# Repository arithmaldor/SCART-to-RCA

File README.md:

# Copyright and Disclaimer
Copyright: Jacob Proctor 2018

This documentation describes Open Hardware and is licensed under the
CERN OHL v. 1.2.

You may redistribute and modify this documentation under the terms of the
CERN OHL v.1.2. (http://ohwr.org/cernohl). This documentation is distributed
WITHOUT ANY EXPRESS OR IMPLIED WARRANTY, INCLUDING OF
MERCHANTABILITY, SATISFACTORY QUALITY AND FITNESS FOR A
PARTICULAR PURPOSE. Please see the CERN OHL v.1.2 for applicable
conditions

# SCART to RCA Board

The goal of this project was to make an affordable open-source way to connect SCART cables to PVMs' or Crosspoint Switches. This is designed so
that the cables will be in line, and you can mount multiple of these boards in a row for crosspoint switches. Use with either RCA cables and RCA
female to male BNC adapters or RCA male to BNC female adapters and BNC cables. Use high quality adapters and cables for best results.

# Parts

SCART Connector: K-SCARTX-024, available on Mouser

RCA Connector: PJRAS3X2S01 is available on Mouser and Digikey, but the colors are wrong. Here are the ones I used, a bit cheaper per part:

https://www.ebay.com/itm/QTY-10-6-WAY-PCB-FEMALE-RCA-JACKS-GREEN-YELLOW-BLUE-WHITE-RED-RED-RCA-268N1-14/112220720415?var=null

Mounting hole size is M3, can be used with motherboard standoffs for mounting on MDF or acrylic or something else.

# Price Breakdown
$7.45 per board from OSHPark

$1.00 per RCA connector

$2.50 per SCART connector

Total per board: ~$11

# Version 0.1
This board is untested, I will probably be ordering a few soon after which I will update the version number to 1.0 if everything works out.

# OSHPark
https://oshpark.com/shared_projects/7CGRR3nm

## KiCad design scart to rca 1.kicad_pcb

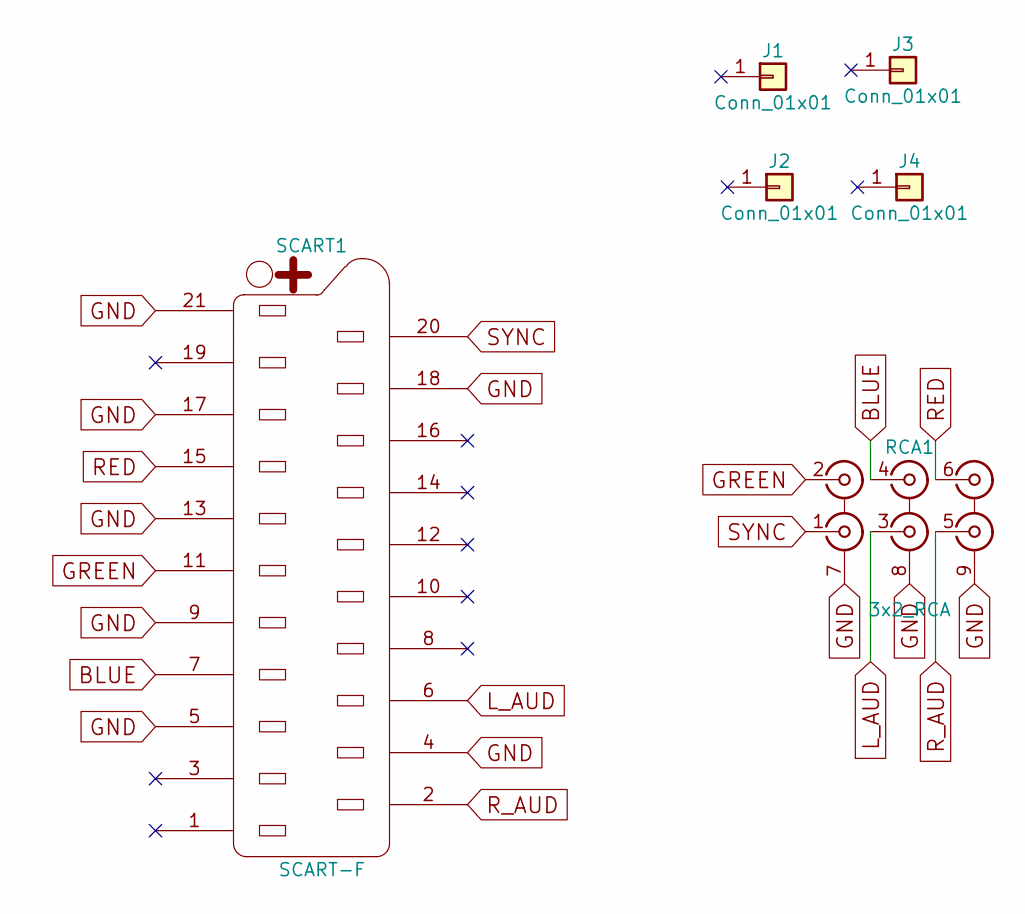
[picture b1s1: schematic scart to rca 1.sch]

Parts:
J1, J2, J3, J4: Conn_01x01; MountingHole_3.2mm_M3
RCA1: 3x2_RCA
SCART1: SCART-F; SCART_F

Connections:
BLUE: RCA1.4 (INGRN), SCART1.7
GND: RCA1.7 (GND), RCA1.8 (GND), RCA1.9 (GND), SCART1.4, SCART1.5, SCART1.9, SCART1.13, SCART1.17, SCART1.18, SCART1.21
GREEN: RCA1.2 (INRED), SCART1.11
L_AUD: RCA1.3 (INLAU), SCART1.6
RED: RCA1.6 (INBLU), SCART1.15
R_AUD: RCA1.5 (INRAU), SCART1.2
SYNC: RCA1.1 (INSYN), SCART1.20

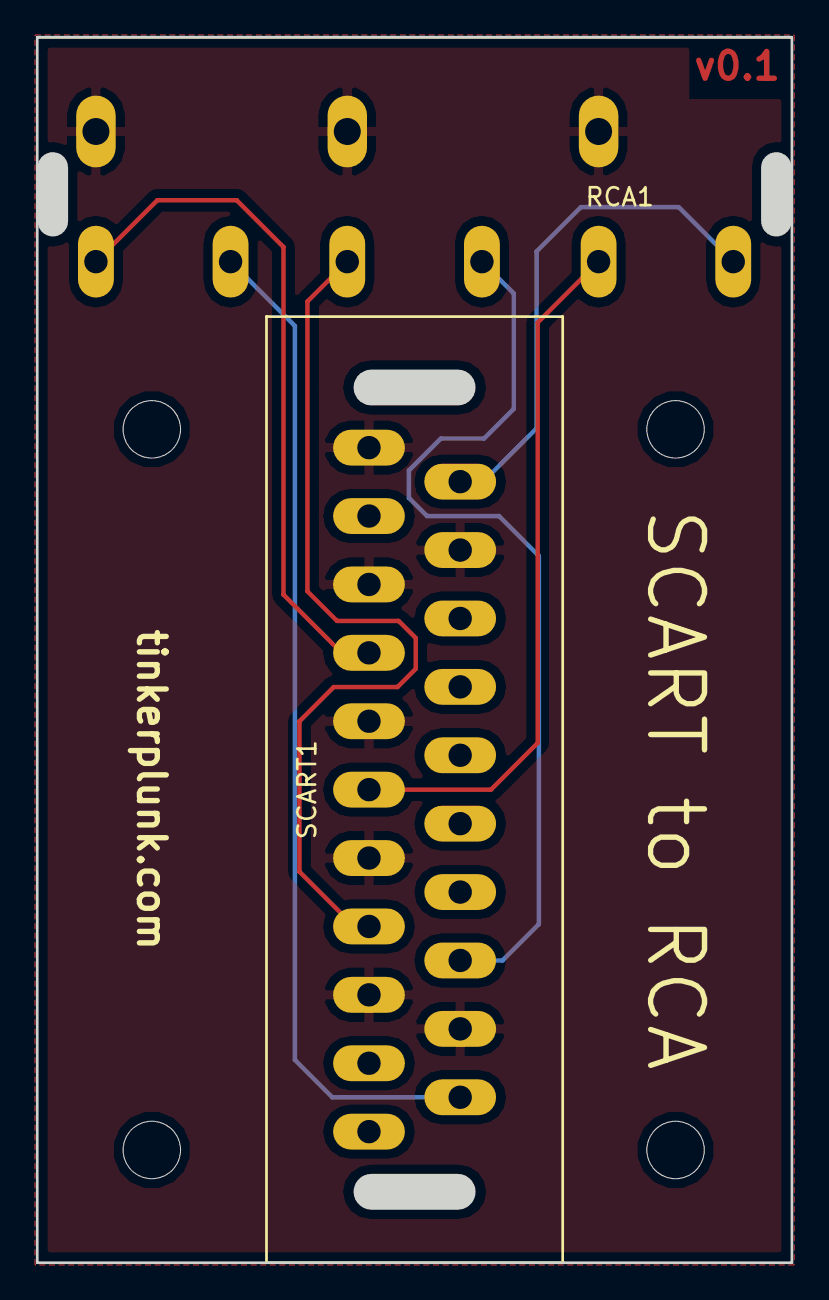
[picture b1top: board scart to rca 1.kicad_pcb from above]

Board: 2 copper layers, 40.2 x 66.4 mm, 6 parts (0 on the bottom side), 7 nets.

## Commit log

2018-06-08 README updated
2018-06-08 updated with correct zip file
